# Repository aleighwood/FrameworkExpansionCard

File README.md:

# FrameworkExpansionCard

This framework expansion card measures ambient C02 concentration, temperature and humidity. It can be used on any computer with a USBC port. Currently, you can view the sensor readings using your preferred serial interface. In the future I will make a nice UI - any maybe automated high C02 level warnings. 

You will need to install the appropriate drivers for the CP2102 chip. Other ICs included an ATMega328 and Sensirion SCD40.

Unfortunately the size of the Sensirion SCD40 IC prohibits the device from fully fitting into the Framework expansion card bay. In the future I will use the newly released Sensirion STCC4 sensor, allowing the device to fit snugly into the expansion card port.

This is a project that I did under the supervision of Professor Mikhelson at Northwestern University (Chicago).

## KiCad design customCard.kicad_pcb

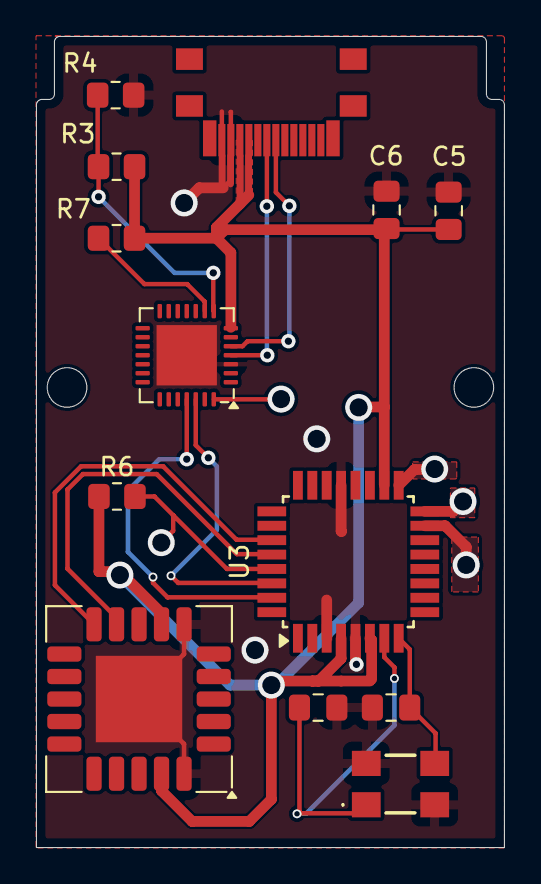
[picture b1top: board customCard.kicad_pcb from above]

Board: 2 copper layers, 26.0 x 45.1 mm, 15 parts (0 on the bottom side), 13 nets.

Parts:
C1: 830030819
C3, C4: 18p; C_0805_2012Metric_Pad1.18x1.45mm_HandSolder
C5: 4.7u; C_0805_2012Metric_Pad1.18x1.45mm_HandSolder
C6: 0.1u; C_0805_2012Metric_Pad1.18x1.45mm_HandSolder
H1, H2: MountingHole; MountingHole_2.2mm_M2
R3: 22.1k; R_0805_2012Metric_Pad1.20x1.40mm_HandSolder
R4: 47.5k; R_0805_2012Metric_Pad1.20x1.40mm_HandSolder
R6: 10k; R_0805_2012Metric_Pad1.20x1.40mm_HandSolder
R7: 1k; R_0805_2012Metric_Pad1.20x1.40mm_HandSolder
U1: framework_adafruit_USBC_connector
U3: ATmega328-A; TQFP-32_7x7mm_P0.8mm
U4: CP2102N-Axx-xQFN28; QFN-28-1EP_5x5mm_P0.5mm_EP3.35x3.35mm
U5: SCD40-D-R2; Sensirion_SCD4x-1EP_10.1x10.1mm_P1.25mm_EP4.8x4.8mm

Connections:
5V_bus: C5.1, C6.1, R3.1, R6.1, R7.1, U1.A4(VBUS) (VBUS), U1.B9(VBUS) (VBUS), U3.4 (VCC), U3.6 (VCC), U3.18 (AVCC), U4.7 (VREGIN), U5.7 (VDD), U5.19 (VDD)
/ATMega RX: U3.30 (PD0), U4.26 (TXD)
/ATMega TX: U3.31 (PD1), U4.25 (RXD)
GND: C1.2 (GND_&_LID_1), C1.4 (GND_&_LID_2), C3.2, C4.2, C5.2, C6.2, R4.2, U1.A1(GND) (GND), U1.B12(GND) (GND), U3.3 (GND), U3.5 (GND), U3.21 (GND), U4.3 (GND), U4.29 (GND), U5.6 (GND), U5.20 (GND), U5.21 (GND)
unnamed: C1.1 (CRYSTAL_1), C3.1, U3.7 (XTAL1/PB6)
unnamed: C1.3 (CRYSTAL_2), C4.1, U3.8 (XTAL2/PB7)
unnamed: U1.A6(D+) (D+), U4.4 (D+)
unnamed: U1.A7(D-) (D-), U4.5 (D-)
unnamed: U3.27 (PC4), U5.10 (SDA)
unnamed: U3.28 (PC5), U5.9 (SCL)
unnamed: R6.2, U3.29 (~RESET/PC6)
unnamed: R3.2, R4.1, U4.8 (VBUS)
unnamed: R7.2, U4.9 (~RST)

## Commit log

2025-06-14 Create mainCode
2025-09-20 initial commit with schematic + PCB layout only
